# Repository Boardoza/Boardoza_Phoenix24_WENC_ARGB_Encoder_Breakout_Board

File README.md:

# Boardoza Phoenix24-WENC Breakout Board

The **Boardoza Phoenix-24WENC** is a versatile **addressable RGB LED breakout board** designed for interactive lighting applications. It integrates **24 addressable ARGB LEDs** along with a **rotary encoder**, enabling users to control lighting effects dynamically through physical input.

This board is well-suited for **user interfaces, decorative lighting, visual feedback systems, and interactive prototypes**. With support for **both CMOS and TTL logic levels** and flexible **THT and SMD connection options**, it can be easily integrated into a wide range of embedded systems, from quick prototyping setups to final product designs.

## [Click here to purchase!](https://www.ozdisan.com/ureticiler/boardoza)
| Front Side | Back Side |
|:---:|:---:|
|  |  |

---

## Key Features

- **24 Addressable ARGB LEDs:** Provides vibrant, individually controllable RGB lighting for dynamic visual effects.  
- **Integrated Rotary Encoder Support:** Enables real-time and interactive LED control through user input.  
- **CMOS & TTL Logic Compatibility:** Ensures compatibility with a wide range of microcontrollers and logic systems.  
- **Flexible Signal Routing:** Includes DIN, CIN, DOUT, and COUT connections for easy signal chaining and management.  
- **Dual Connection Options:** Supports both THT (Through-Hole) and SMD (Surface-Mount) connections for flexible integration.  
- **Interactive Lighting Capabilities:** Ideal for user interfaces, visual feedback, and decorative lighting systems.  

---

## Technical Specifications

**Model:** Phoenix-24WENC   
**Manufacturer:** Boardoza  
**Functions:** Addressable RGB LED control with rotary encoder input  
**Input Voltage:** 3.3 V / 5 V  
**LED Model:** T3A33BRG-H9C0002X1U1930  
**Number of LEDs:** 24  
**LED Type:** Individually addressable RGB LEDs  
**Logic Compatibility:** TTL & CMOS  
**Data Interface:** Serial Data & Clock (DIN / CIN / DOUT / COUT)   
**Encoder Outputs:** Terminal A, Terminal B, Switch (Active Low)  
**Daisy-Chain Support:** Yes   
**Operating Temperature:** -40 °C to +85 °C  
**Board Dimensions:** 65.93 mm × 66.18 mm  

---

## Board Pinout

### **( J1 ) Power Connector**

| Pin Number | Pin Name | Description |
|:---:|:---:|---|
| 1 | VCC | Power Supply |

### **( J2 ) Power Connector**

| Pin Number | Pin Name | Description |
|:---:|:---:|---|
| 2 | VCC | Power Supply |

### **( J3 ) Encoder Terminal B**

| Pin Number | Pin Name | Description |
|:---:|:---:|---|
| 3 | Terminal_B | Encoder B terminal output |

### **( J4 ) Encoder Terminal A**

| Pin Number | Pin Name | Description |
|:---:|:---:|---|
| 4 | Terminal_A | Encoder A terminal output |

### **( J5 ) Encoder Switch**

| Pin Number | Pin Name | Description |
|:---:|:---:|---|
| 5 | SW | Encoder switch output (Active Low) |

### **( J6 ) Data Output**

| Pin Number | Pin Name | Description |
|:---:|:---:|---|
| 6 | DOUT | Series data output |

### **( J7 ) Clock Output**

| Pin Number | Pin Name | Description |
|:---:|:---:|---|
| 7 | COUT | Clock output |

### **( J8 ) Data Input**

| Pin Number | Pin Name | Description |
|:---:|:---:|---|
| 8 | DIN | Series data input |

### **( J9 ) Clock Input**

| Pin Number | Pin Name | Description |
|:---:|:---:|---|
| 9 | CIN | Clock input |

### **( J10 ) Ground**

| Pin Number | Pin Name | Description |
|:---:|:---:|---|
| 10 | GND | Ground |

### **( J11 ) Ground**

| Pin Number | Pin Name | Description |
|:---:|:---:|---|
| 11 | GND | Ground |

---

## Board Dimensions

---

## Step Files

[Boardoza Phoenix-24WENC.step](./assets/Phoenix-24WENC%20Step.step)

---

## Datasheets

- [T3A33BRG ARGB LED Datasheet](./assets/Phoenix-24WENC%20Datasheet.pdf)  
- [Rotary Encoder Datasheet](./assets/Rotary%20Encoder%20Datasheet.pdf)

---

## Version History

- V1.0.0 – Initial Release

---

## Support

- If you have any questions or need support, please contact **support@boardoza.com**

---

## **License**

This repository contains both hardware and software components:

### **Hardware Design**

[![CC BY-SA 4.0][cc-by-sa-shield]][cc-by-sa]

All hardware design files are licensed under [Creative Commons Attribution-ShareAlike 4.0 International License][cc-by-sa].

[cc-by-sa]: http://creativecommons.org/licenses/by-sa/4.0/
[cc-by-sa-shield]: https://img.shields.io/badge/License-CC%20BY--SA%204.0-lightgrey.svg

### **Software/Firmware**

[![BSD-3-Clause][bsd-shield]][bsd]

All software and firmware are licensed under [BSD 3-Clause License][bsd].

[bsd]: https://opensource.org/licenses/BSD-3-Clause
[bsd-shield]: https://img.shields.io/badge/License-BSD%203--Clause-blue.svg

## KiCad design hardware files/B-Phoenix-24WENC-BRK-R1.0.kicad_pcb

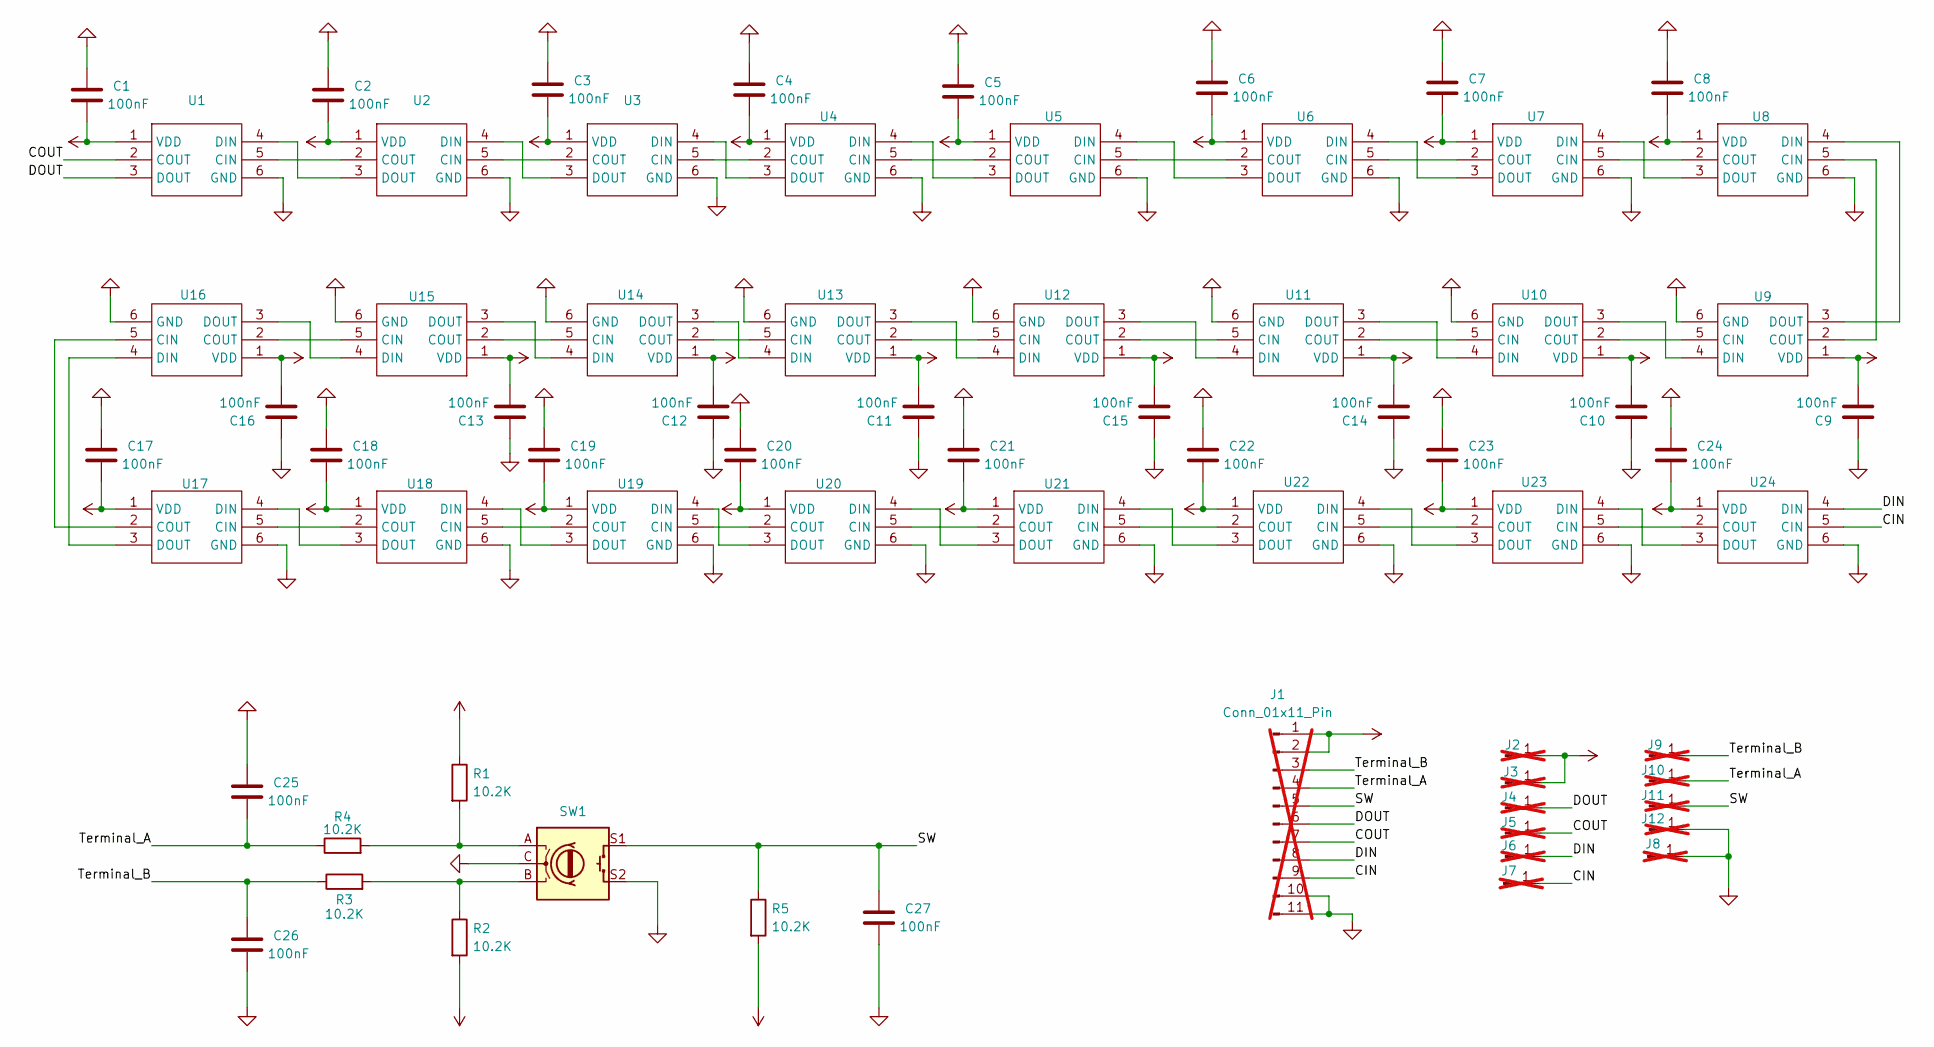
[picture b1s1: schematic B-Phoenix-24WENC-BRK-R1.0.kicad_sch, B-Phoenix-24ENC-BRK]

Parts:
C1, C2, C3, C4, C5, C6, C7, C8, C9, C10, C11, C12, C13, C14, C15, C16, C17, C18, C19, C20, C21, C22, C23, C24, C25, C26, C27: 100nF; C_0603_1608Metric; MPN MCF03KTB500104
J1: Conn_01x11_Pin; PinSocket_1x11_P2.54mm_Vertical; not fitted
J2, J3, J4, J5, J6, J7, J8, J9, J10, J11, J12: Conn_01x01_Pin; SolderWirePad_1x01_SMD_5x10mm; not fitted
R1, R2, R3, R4, R5: 10.2K; R_0603_1608Metric; MPN 0603SAF1022T5E
SW1: RotaryEncoder_Switch; L-KLS4-EC1123S-E-5A-F20; MPN L-KLS4-EC1123S-E-5A-F20
U1, U2, U3, U4, U5, U6, U7, U8, U9, U10, U11, U12, U13, U14, U15, U16, U17, U18, U19, U20, U21, U22, U23, U24: T3A33BRG-H9C0002X1U1930_HVK; MPN T3A33BRG-H9C0002X1U1930

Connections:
/CIN: J1.9, J7.1, U24.5 (CIN)
/COUT: J1.7, J5.1, U1.2 (COUT)
/DIN: J1.8, J6.1, U24.4 (DIN)
/DOUT: J1.6, J4.1, U1.3 (DOUT)
/SW: C27.1, J1.5, J11.1, R5.1, SW1.S1
/Terminal_A: C25.2, J1.4, J10.1, R4.1
/Terminal_B: C26.1, J1.3, J9.1, R3.1
GND: C1.1, C2.1, C3.1, C4.1, C5.1, C6.1, C7.1, C8.1, C9.1, C10.1, C11.1, C12.1, C13.1, C14.1, C15.1, C16.1, C17.1, C18.1, C19.1, C20.1, C21.1, C22.1, C23.1, C24.1, C25.1, C26.2, C27.2, J1.10, J1.11, J8.1, J12.1, SW1.C, SW1.MP, SW1.S2, U1.6 (GND), U2.6 (GND), U3.6 (GND), U4.6 (GND), U5.6 (GND), U6.6 (GND), U7.6 (GND), U8.6 (GND), U9.6 (GND), U10.6 (GND), U11.6 (GND), U12.6 (GND), U13.6 (GND), U14.6 (GND), U15.6 (GND), U16.6 (GND), U17.6 (GND), U18.6 (GND), U19.6 (GND), U20.6 (GND), U21.6 (GND), U22.6 (GND), U23.6 (GND), U24.6 (GND)
unnamed: R1.2, R4.2, SW1.A
unnamed: R2.1, R3.2, SW1.B
unnamed: U1.5 (CIN), U2.2 (COUT)
unnamed: U1.4 (DIN), U2.3 (DOUT)
unnamed: U2.5 (CIN), U3.2 (COUT)
unnamed: U2.4 (DIN), U3.3 (DOUT)
unnamed: U3.5 (CIN), U4.2 (COUT)
unnamed: U3.4 (DIN), U4.3 (DOUT)
unnamed: U4.5 (CIN), U5.2 (COUT)
unnamed: U4.4 (DIN), U5.3 (DOUT)
unnamed: U5.5 (CIN), U6.2 (COUT)
unnamed: U5.4 (DIN), U6.3 (DOUT)
unnamed: U6.5 (CIN), U7.2 (COUT)
unnamed: U6.4 (DIN), U7.3 (DOUT)
unnamed: U7.5 (CIN), U8.2 (COUT)
unnamed: U7.4 (DIN), U8.3 (DOUT)
unnamed: U8.5 (CIN), U9.2 (COUT)
unnamed: U8.4 (DIN), U9.3 (DOUT)
unnamed: U10.5 (CIN), U11.2 (COUT)
unnamed: U9.5 (CIN), U10.2 (COUT)
unnamed: U10.4 (DIN), U11.3 (DOUT)
unnamed: U9.4 (DIN), U10.3 (DOUT)
unnamed: U11.5 (CIN), U12.2 (COUT)
unnamed: U11.4 (DIN), U12.3 (DOUT)
unnamed: U12.5 (CIN), U13.2 (COUT)
unnamed: U12.4 (DIN), U13.3 (DOUT)
unnamed: U13.5 (CIN), U14.2 (COUT)
unnamed: U13.4 (DIN), U14.3 (DOUT)
unnamed: U14.5 (CIN), U15.2 (COUT)
unnamed: U14.4 (DIN), U15.3 (DOUT)
unnamed: U15.5 (CIN), U16.2 (COUT)
unnamed: U15.4 (DIN), U16.3 (DOUT)
unnamed: U16.5 (CIN), U17.2 (COUT)
unnamed: U16.4 (DIN), U17.3 (DOUT)
unnamed: U17.5 (CIN), U18.2 (COUT)
unnamed: U17.4 (DIN), U18.3 (DOUT)
unnamed: U18.5 (CIN), U19.2 (COUT)
unnamed: U18.4 (DIN), U19.3 (DOUT)
unnamed: U19.5 (CIN), U20.2 (COUT)
unnamed: U19.4 (DIN), U20.3 (DOUT)
unnamed: U20.5 (CIN), U21.2 (COUT)
unnamed: U20.4 (DIN), U21.3 (DOUT)
unnamed: U21.5 (CIN), U22.2 (COUT)
unnamed: U21.4 (DIN), U22.3 (DOUT)
unnamed: U22.5 (CIN), U23.2 (COUT)
unnamed: U22.4 (DIN), U23.3 (DOUT)
unnamed: U23.5 (CIN), U24.2 (COUT)
unnamed: U23.4 (DIN), U24.3 (DOUT)
VCC: C1.2, C2.2, C3.2, C4.2, C5.2, C6.2, C7.2, C8.2, C9.2, C10.2, C11.2, C12.2, C13.2, C14.2, C15.2, C16.2, C17.2, C18.2, C19.2, C20.2, C21.2, C22.2, C23.2, C24.2, J1.1, J1.2, J2.1, J3.1, R1.1, R2.2, R5.2, U1.1 (VDD), U2.1 (VDD), U3.1 (VDD), U4.1 (VDD), U5.1 (VDD), U6.1 (VDD), U7.1 (VDD), U8.1 (VDD), U9.1 (VDD), U10.1 (VDD), U11.1 (VDD), U12.1 (VDD), U13.1 (VDD), U14.1 (VDD), U15.1 (VDD), U16.1 (VDD), U17.1 (VDD), U18.1 (VDD), U19.1 (VDD), U20.1 (VDD), U21.1 (VDD), U22.1 (VDD), U23.1 (VDD), U24.1 (VDD)

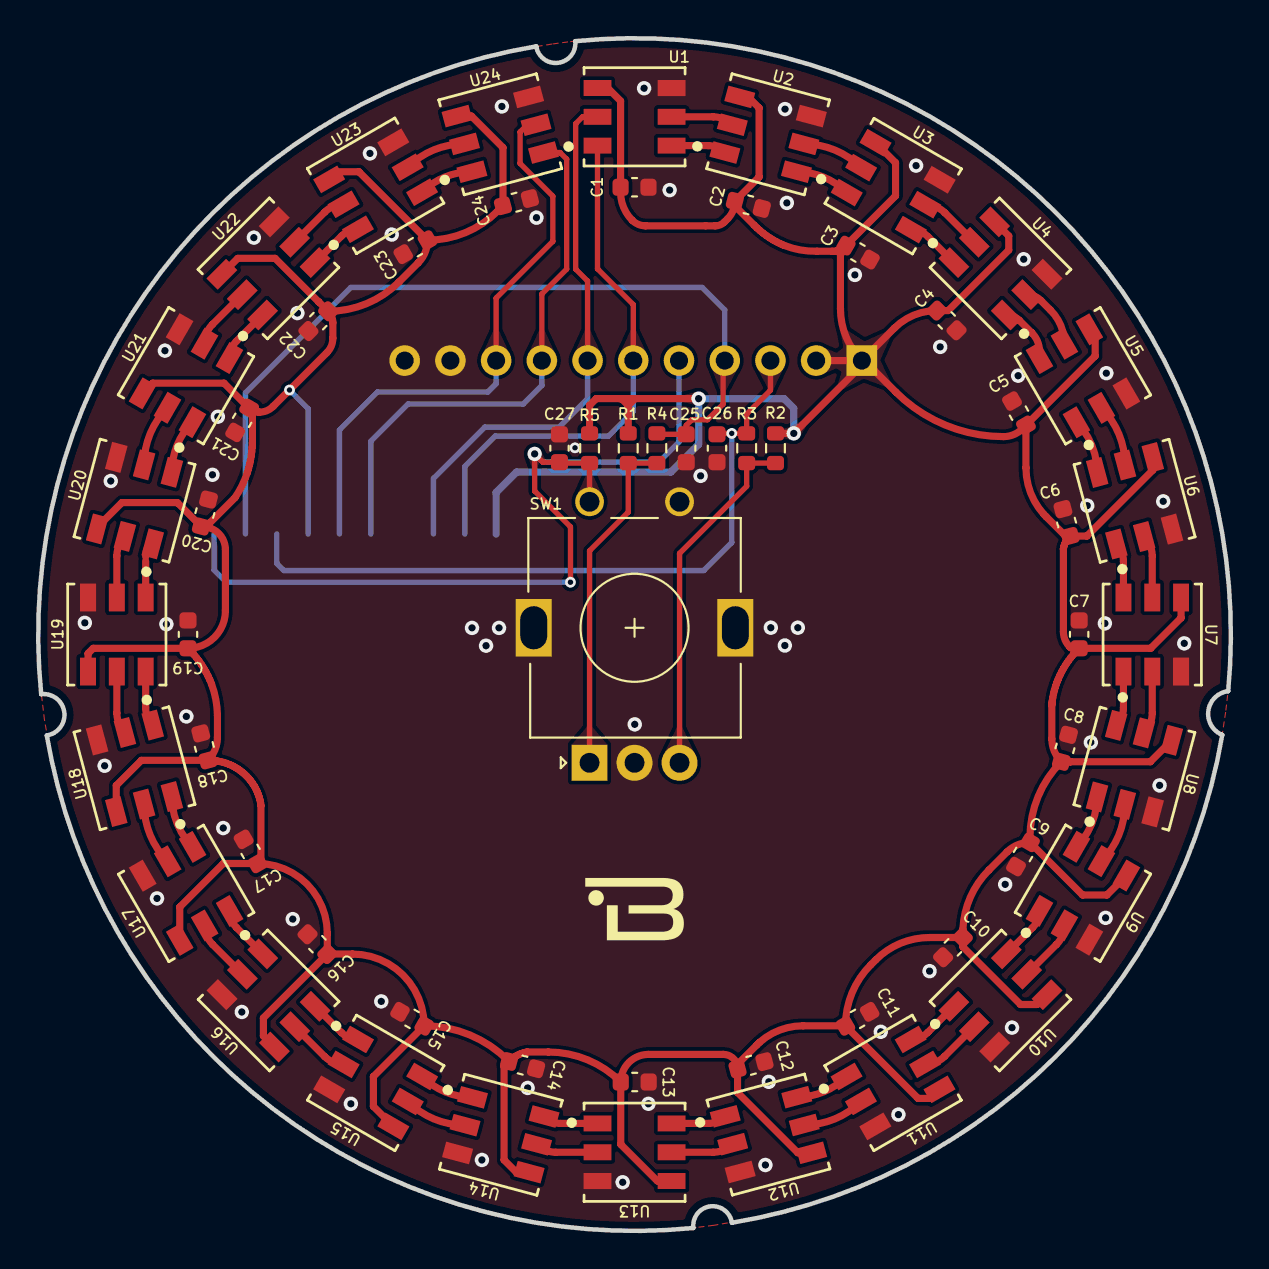
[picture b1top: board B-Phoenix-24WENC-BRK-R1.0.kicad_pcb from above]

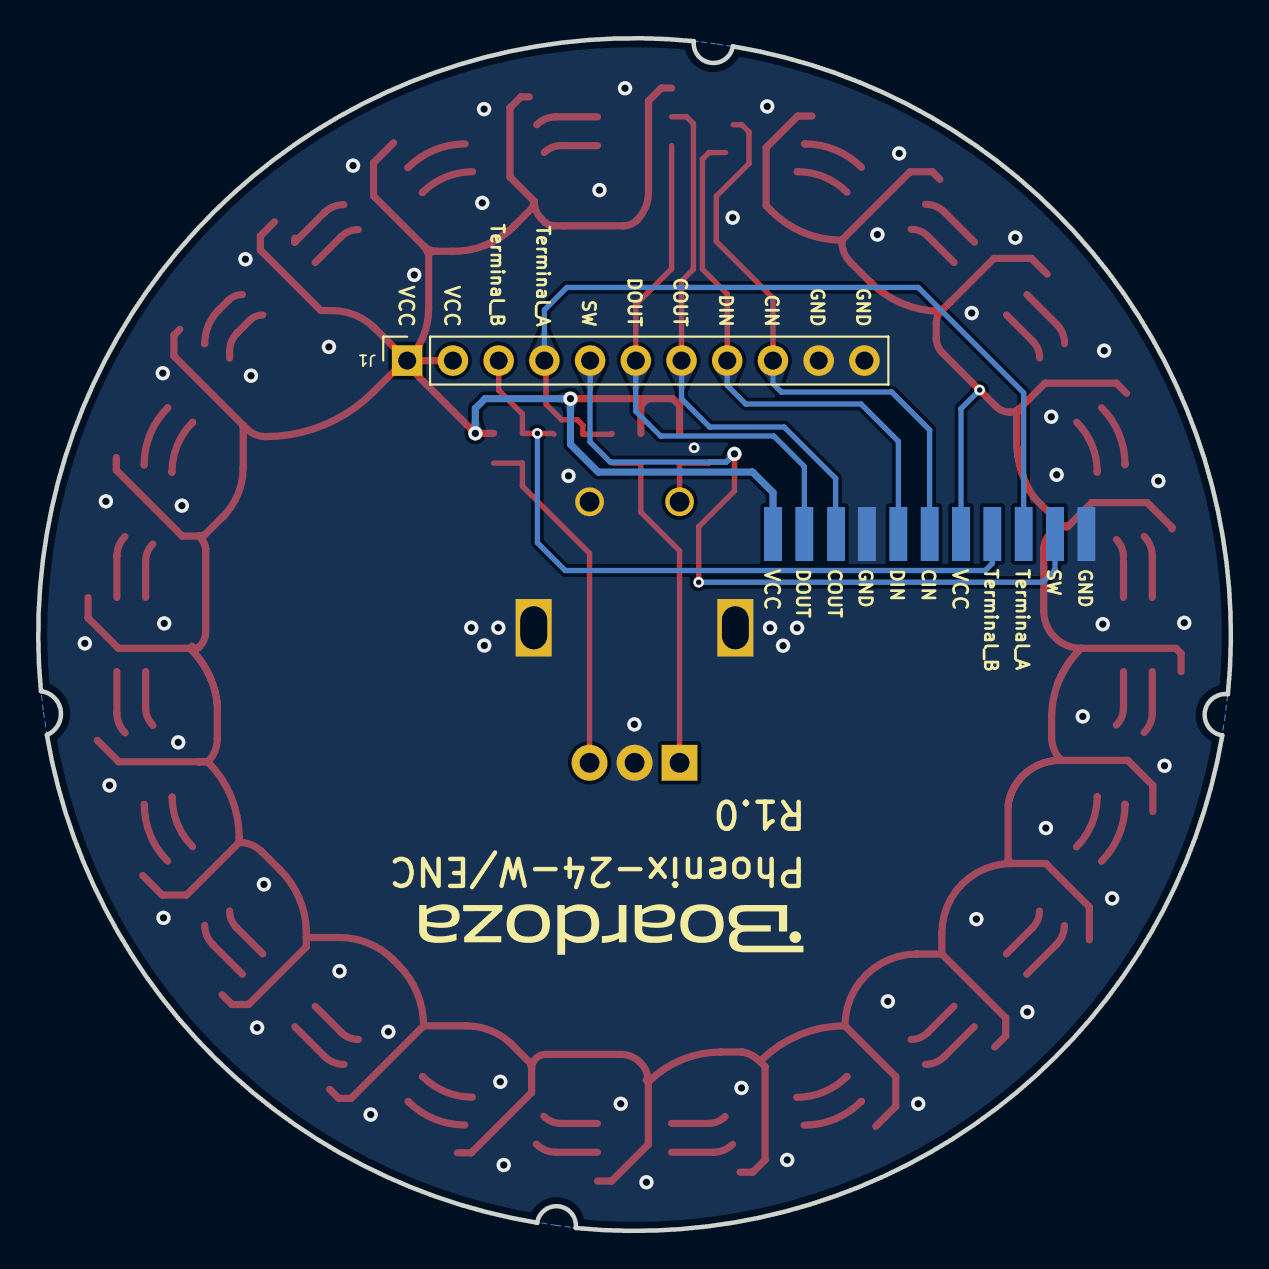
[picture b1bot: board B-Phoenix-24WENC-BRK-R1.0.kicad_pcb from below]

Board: 2 copper layers, 66.3 x 66.3 mm, 69 parts (12 on the bottom side), 57 nets.

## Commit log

2026-04-28 Fix hueOffset declaration formatting
2026-04-28 Fixed comment lines
2026-04-28 Refactor comments in EC1101S.cpp for clarity
    Updated comments for clarity and consistency, translating some comments to English.
